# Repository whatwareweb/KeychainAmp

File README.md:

# KeychainAmp

Audio amplifier on a keychain based on lm326

For more details, see [journal.md](journal.md)!

BOM:

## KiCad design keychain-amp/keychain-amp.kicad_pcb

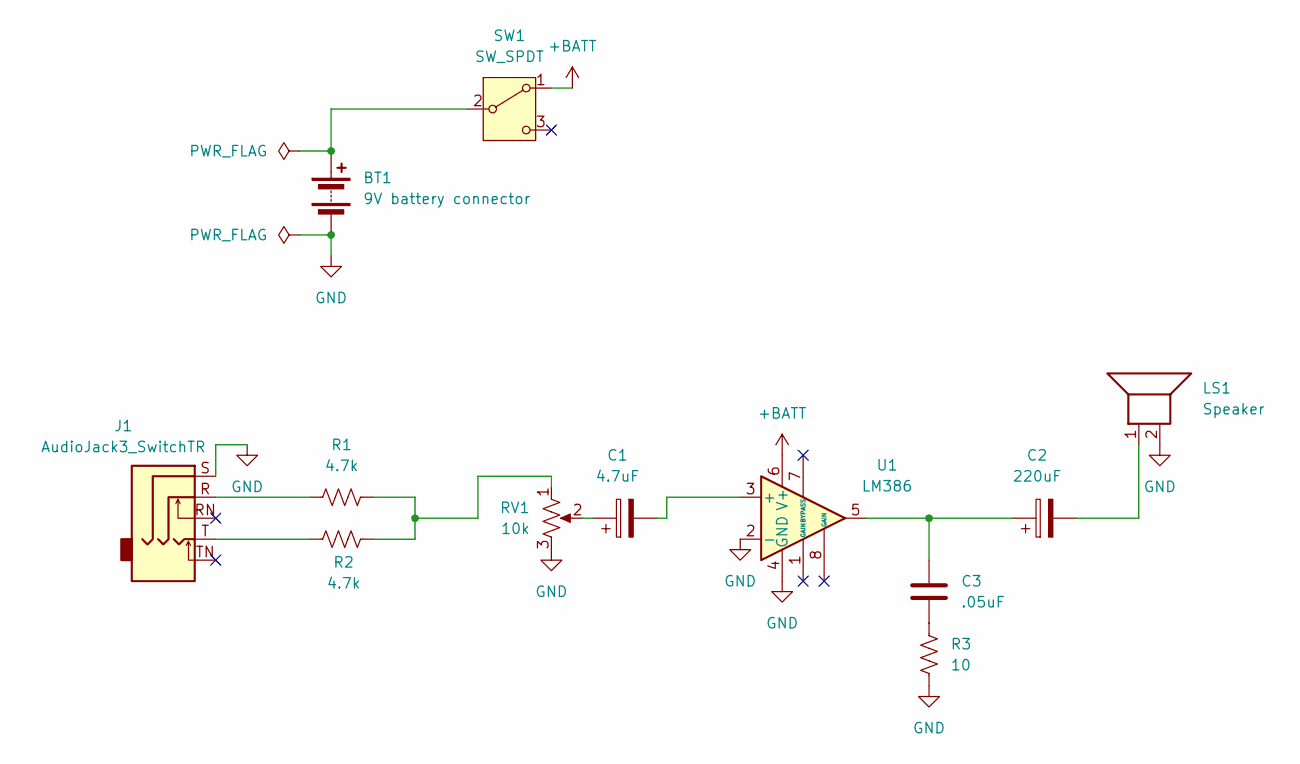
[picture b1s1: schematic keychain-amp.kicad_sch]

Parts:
BT1: 9V battery connector; PinHeader_1x02_P2.54mm_Vertical
C1: 4.7uF; CP_Radial_D5.0mm_P2.00mm; Mouser PN 710-860010572001
C2: 220uF; CP_Radial_D6.3mm_P2.50mm; Mouser PN 710-860010473011
C3: .05uF; C_1206_3216Metric_Pad1.33x1.80mm_HandSolder; Mouser PN 581-12065C503JAT2A
J1: AudioJack3_SwitchTR; Jack_3.5mm_CUI_SJ-3524-SMT_Horizontal; Mouser PN 490-SJ-3524-SMT-TR
LS1: Speaker; TestPoint_Bridge_Pitch7.62mm_Drill1.3mm
R1, R2: 4.7k; R_Axial_DIN0207_L6.3mm_D2.5mm_P10.16mm_Horizontal
R3: 10; R_Axial_DIN0207_L6.3mm_D2.5mm_P10.16mm_Horizontal
RV1: 10k; Potentiometer_Bourns_PTA1543_Single_Slide; Mouser PN 652-PTA15432015CPB10
SW1: SW_SPDT; SW_Slide_SPDT_Angled_CK_OS102011MA1Q; Mouser PN 179-SLW8645872ARAND
U1: LM386; DIP-8_W7.62mm; Mouser PN 926-LM386N-1/NOPB

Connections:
+BATT: SW1.1 (A), U1.6 (V+)
GND: BT1.2 (-), J1.S, LS1.2, R3.2, RV1.3, U1.2 (-), U1.4 (GND)
unnamed: BT1.1 (+), SW1.2 (B)
unnamed: C1.1, RV1.2
unnamed: C2.1, C3.1, U1.5
unnamed: C2.2, LS1.1
unnamed: C3.2, R3.1
unnamed: J1.R, R1.1
unnamed: J1.T, R2.1
unnamed: R1.2, R2.2, RV1.1
unnamed: C1.2, U1.3 (+)

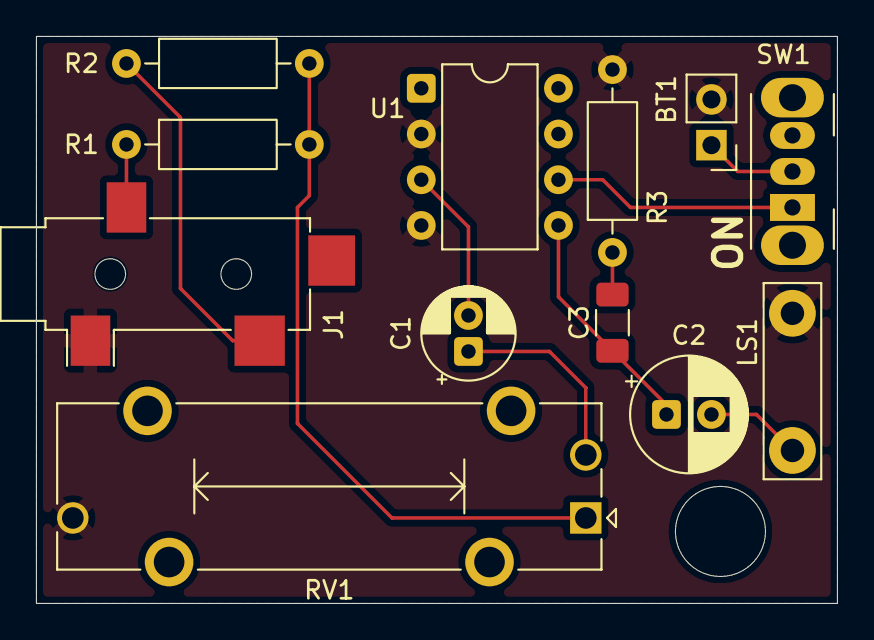
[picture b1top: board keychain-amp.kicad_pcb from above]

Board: 2 copper layers, 44.5 x 31.5 mm, 12 parts (0 on the bottom side), 11 nets.

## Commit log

2026-06-18 create kicad project
